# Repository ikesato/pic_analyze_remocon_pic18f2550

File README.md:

概要
====
家庭用リモコン信号を受信しコードを解析する。  
また解析したコードを送信し解析したコードのテストを可能とする。  

- マイコン : PIC18F2550
- USB接続 (CDC クラスを使用)
- CDC Basic Demo をベースに赤外線LEDの送受信し、データをシリアル通信で送受信
- 赤外通信 38KHz
- 解析できるコードは家電協フォーマット、ソニーフォーマット
- 受信と解析  
 リモコン -> 赤外線受光部 -> マイコン -> PCでコードを解析
- 送信  
 PC -> マイコン -> 赤外LEDで送信
- フリスクケースに収まるサイズで作成

回路図
=====

配線
====

部品
====
- LED x 2
- 赤外線LED x 2
 型番 : TLN105B
- 赤外線受光モジュール  
 型番 : PL-IRM2161-C438
- FET  
 型番 : 2SK2201
- 水晶振動子 20MHz
- マイコン : PIC18F2550 DIP 28ピン
- USBコネクタ変換基板  
 型番 : サンハヤト CK-37  
 ケースに収めるため一部カット加工
- スイッチ （モーメンタリ） x 2
- コンデンサ 0.1uF x 2
- 抵抗  
 1KΩ  (チップ抵抗) x 2  
 1Ω  x 1  
 10KΩ  x 2  

使用方法
========

1. 接続  
 マイコン部とPCをUSBケーブルで接続する。  
 USBから電源供給をおこなう。  
2. PCでリモコン解析用ツールを起動する  
 `$ ruby serial/ranalyzer.rb /dev/tty.usbXXXXXX`  
 /dev/tty.usbXXXXXX にはシリアルポートデバイスを指定
 Mac の場合は ls /dev/tty.usb* に存在するデバイス
3. 家庭用リモコンをマイコン部に向けて何かボタンを押す
4. 改正気結果がコンソールに表示
5. 解析結果の行をコピー＆ペーストで、そのコードの送信テストが可能
6. ボタンの説明
 - SW1  
  リセットボタン
 - SW2  
  最後に受信または送信したリモコンコードを送信。  
  ２秒長押しで赤外線受信の ON/OFF を切り替え。（テレビが付いている場合、テレビの映像に反応してしまうような場合に赤外線受信をOFFにして使うと便利です）  
 - SW2 を先に押した状態にし、SW1 を押すとファームウェア書き換えモードになる。  
  HIDBootloader などでファームを書き換える事が可能。  

ディレクトリ構成
================

- Firmware ディレクトリ  
 ファームウェアの全ソースコード
- inf ディレクトリ  
 Windows の場合の USBドライバ （動作未確認）
- serial ディレクトリ  
 リモコン解析ツール  
 ruby 製です。1.9.x で作成してますが、たぶん 1.8.x , 2.x でも動くはず。  
 - 必要な gem  
  serialport, optparse
- hex ファイル  
 Firmware/MPLAB.X/dist/PICDEM_FSUSB/production/MPLAB.X.production.hex

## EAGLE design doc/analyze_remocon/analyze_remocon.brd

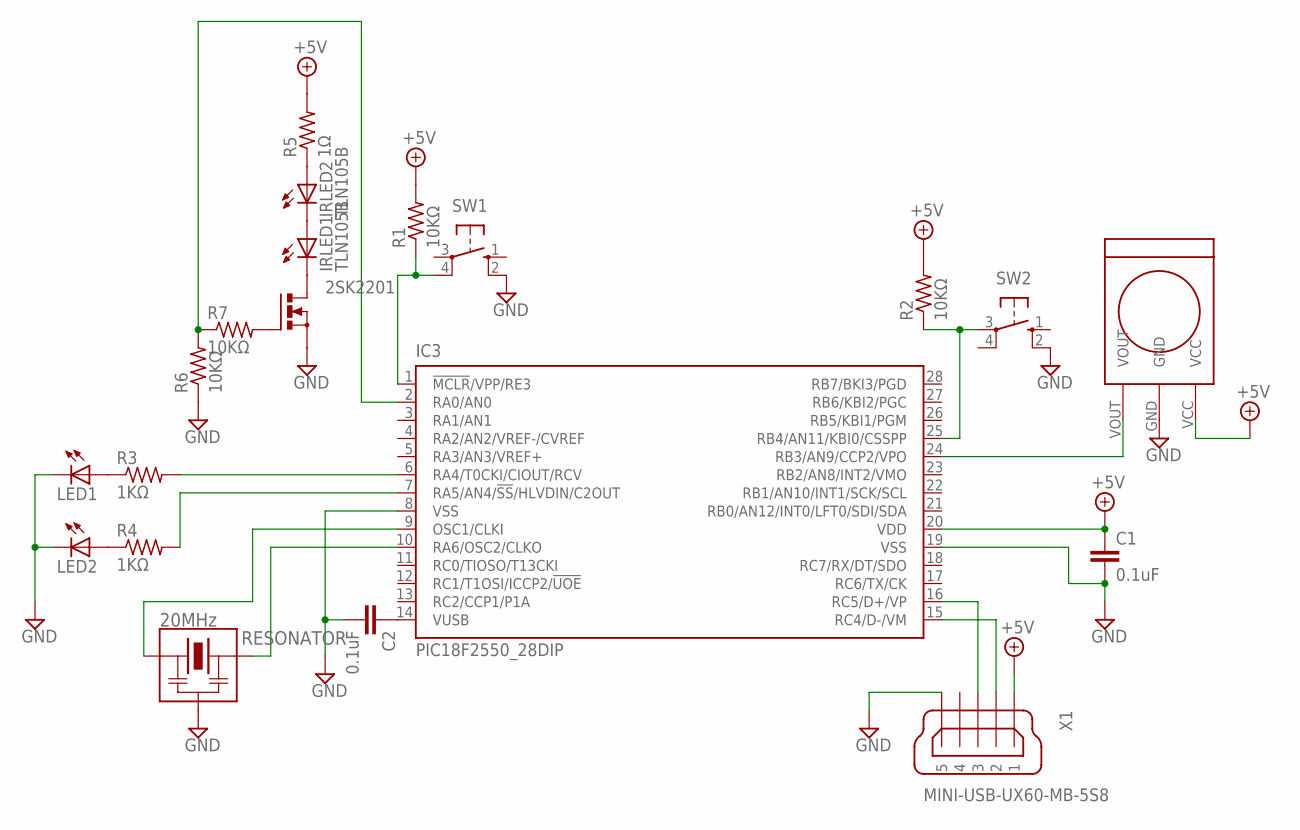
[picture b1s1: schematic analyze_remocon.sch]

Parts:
2SK2201: BUZ11BV; TO220BV
C1, C2: 0.1uF; C025-024X044
IC3: PIC18F2550_28DIP; DIL28-3
IRLED1, IRLED2: TLN105B; LED3MM
LED1, LED2: LED3MM
PL-IRM2161-C438: IRM2161; PL-IRM2161-C438
R1, R2: 10KΩ; MINI_MELF-0102R
R3, R4: 1KΩ; MINI_MELF-0102R
R5: 1Ω; 0207/7
R6, R7: 10KΩ; 0207/7
RESONATOR: 20MHz; HC-49G
SW1, SW2: 10-XX; B3F-10XX
X1: MINI-USB-UX60-MB-5S8; UX60-MB-5S8

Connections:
20MHZ: IC3.9 (OSC1/CLKI), RESONATOR.P1 (LFT)
BLOCK: C1.1, IC3.20 (VDD), PL-IRM2161-C438.VCC, R1.2, R2.2, R5.2, X1.1
GND: 2SK2201.S, C1.2, C2.2, IC3.8 (VSS), IC3.19 (VSS), LED1.K (C), LED2.K (C), PL-IRM2161-C438.GND, R6.1, RESONATOR.CENT (GND), SW1.2 (S1), SW2.2 (S1), X1.5
unnamed: IC3.15 (RC4/D-/VM), X1.2
unnamed: IC3.16 (RC5/D+/VP), X1.3
unnamed: C2.1, IC3.14 (VUSB)
unnamed: IC3.1 (!MCLR!/VPP/RE3), R1.1, SW1.4 (P1)
unnamed: IC3.25 (RB4/AN11/KBI0/CSSPP), R2.1, SW2.3
unnamed: IC3.10 (RA6/OSC2/CLKO), RESONATOR.P2 (RIT)
unnamed: IC3.6 (RA4/T0CKI/CIOUT/RCV), R3.2
unnamed: LED1.A, R3.1
unnamed: IC3.7 (RA5/AN4/!SS!/HLVDIN/C2OUT), R4.2
unnamed: LED2.A, R4.1
unnamed: IC3.2 (RA0/AN0), R6.2, R7.1
unnamed: IRLED2.A, R5.1
unnamed: IRLED1.A, IRLED2.K (C)
unnamed: 2SK2201.D, IRLED1.K (C)
unnamed: 2SK2201.G, R7.2
unnamed: IC3.24 (RB3/AN9/CCP2/VPO), PL-IRM2161-C438.VOUT

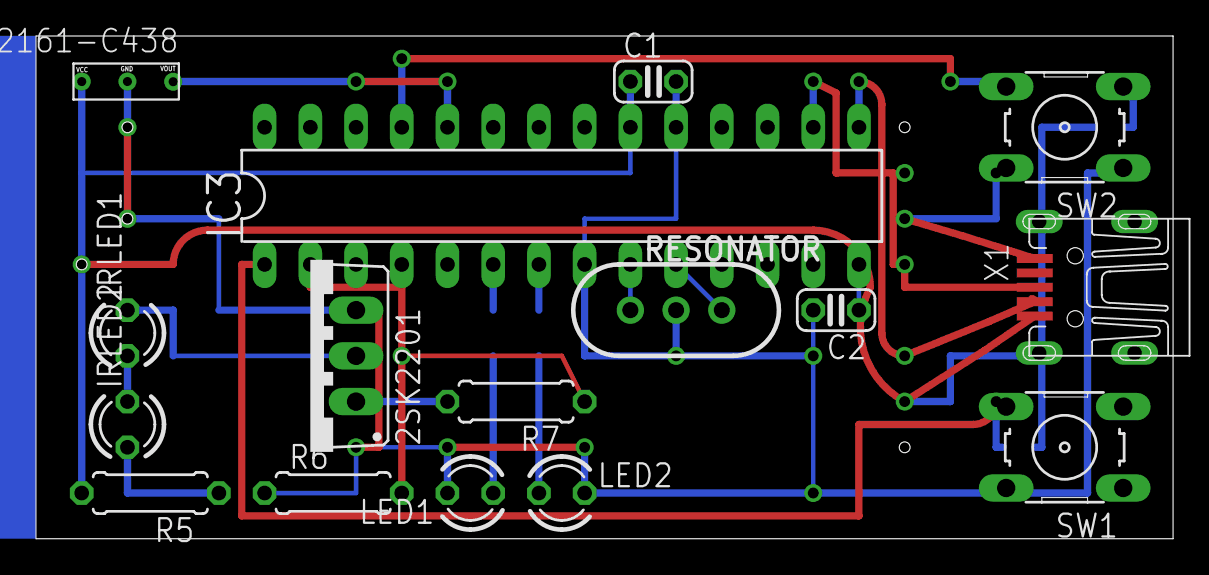
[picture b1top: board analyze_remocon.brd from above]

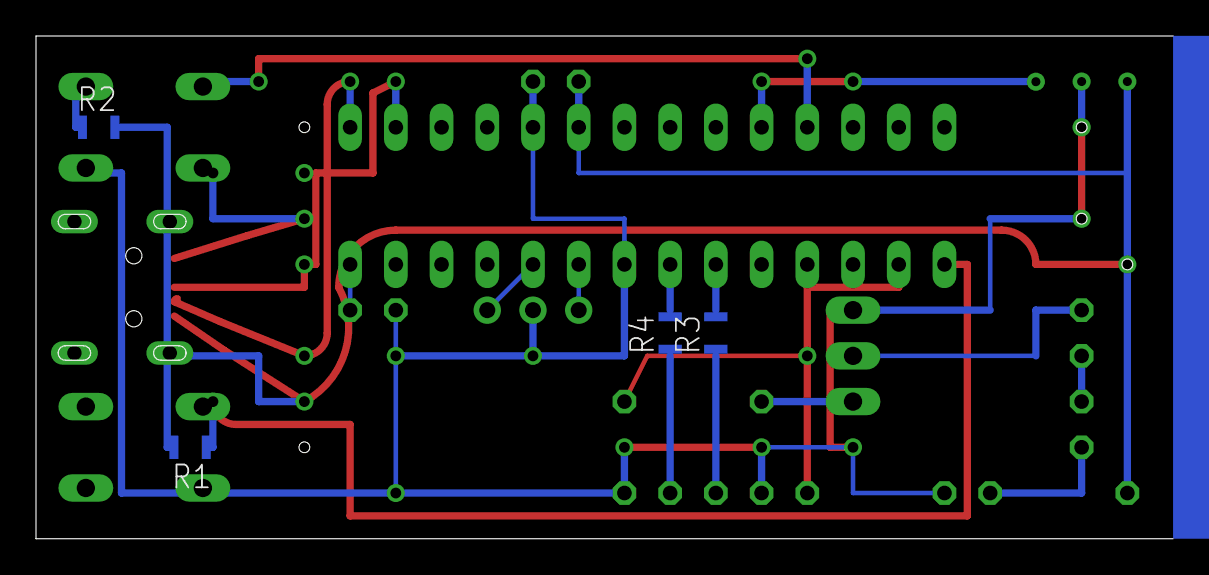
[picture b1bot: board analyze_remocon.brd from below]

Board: 2 copper layers, 63.2 x 27.9 mm, 20 parts (4 on the bottom side), 19 nets.

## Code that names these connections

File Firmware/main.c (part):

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#define SW_TRIS     TRISBbits.TRISB4
#define IRLED_TRIS  TRISAbits.TRISA0

#define LED1_PORT   PORTAbits.RA4
#define LED2_PORT   PORTAbits.RA5
#define IR_PORT     PORTBbits.RB3
#define SW_PORT     PORTBbits.RB4
#define IRLED_PORT  PORTAbits.RA0

#define SW_BIT		(1<<4)

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
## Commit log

2012-10-09 change project name and include path
2012-10-10 change pic writer to PICkit2
2012-10-10 add IR receiver and refeine initilize codes.
2012-10-10 add timer and debug codes.
2012-10-11 implementing...
2012-10-12 add comment
2012-10-14 defined io port macro
2012-10-14 refined timer
2012-10-15 add send ir
2012-10-15 change inteval
2012-10-16 implemented WaitToReadySerial
2012-10-17 torizezu commit. mada send ir de freeze suru
2012-10-18 reassign ram maps
2012-10-18 change cr code only to 0x0a (unix)
2012-10-18 toriaezu
2012-10-21 compressed IR buffer implementation
2012-10-21 add air conditioner codes
2012-10-22 supported HID Bootloader
2012-10-23 add eagle document
2012-10-23 change few 38KHz interval
2012-10-25 change correct hi and lo frequency
2012-10-25 add one LED and change IO port
2012-10-26 add button implementation
2012-10-26 add to enable reading IR mode
2012-10-26 remove unnecessary comment codes
2012-11-15 remove unnecechange duty ratio to 50%
2012-11-16 change duty ratio to 1/3 and stop trailer signal
2012-11-18 update circuit diagram documents
2012-11-20 add circuit diagram image
2012-11-25 update circuit diagram documents. fix D+ D- line.
2012-11-25 implement to read serial command and send ir
2012-11-25 remove warnnings
2012-11-25 add serial ruby interface. and fix to receive serial data problem.
2012-11-25 update remocon data
2012-11-26 change to dump IR buffer format
2012-11-26 fix mojibake at first time.
2012-11-27 add remocon analyzer scripts
2012-11-28 implement SonyFormat
2012-11-29 renamed serial.rb ranalyzer.rb
2012-11-29 add help
2012-11-29 change function name from send_xx to make_send_xx
2012-11-29 add nec format
2012-11-30 show help when ARGV.empty? == true
2012-12-03 change dump format at sony_format
2012-12-04 change dump format
2012-12-04 implement raw format
2012-12-04 implement JVC format
2012-12-04 add absolute path to
2012-12-04 remove unncessary comment
2012-12-04 skip trailer comment in IR input string
2012-12-04 update document and crawl remocon datas
2012-12-04 change indent
2012-12-04 remove unnecessary text
2012-12-05 change format name to upper case
2012-12-05 implement nec repeater format
2012-12-05 remove unnecessary files
2012-12-05 add daikin_format and change filename from fixnum_ary.rb to int_ary.rb
2012-12-07 supported body0 only (no body1,body2)
2012-12-07 write daikin format
2012-12-09 add to_hex
2012-12-09 toriezu
2012-12-09 implement body2
2012-12-11 implement verify and verbose
2012-12-18 implement body2 format
2013-06-02 change control codes
2013-06-02 add schematic image
2013-06-02 modified README.md
2013-06-02 modified image link
2013-06-02 modified README.md and add hex file
2013-07-16 write button's specification and few text modified
